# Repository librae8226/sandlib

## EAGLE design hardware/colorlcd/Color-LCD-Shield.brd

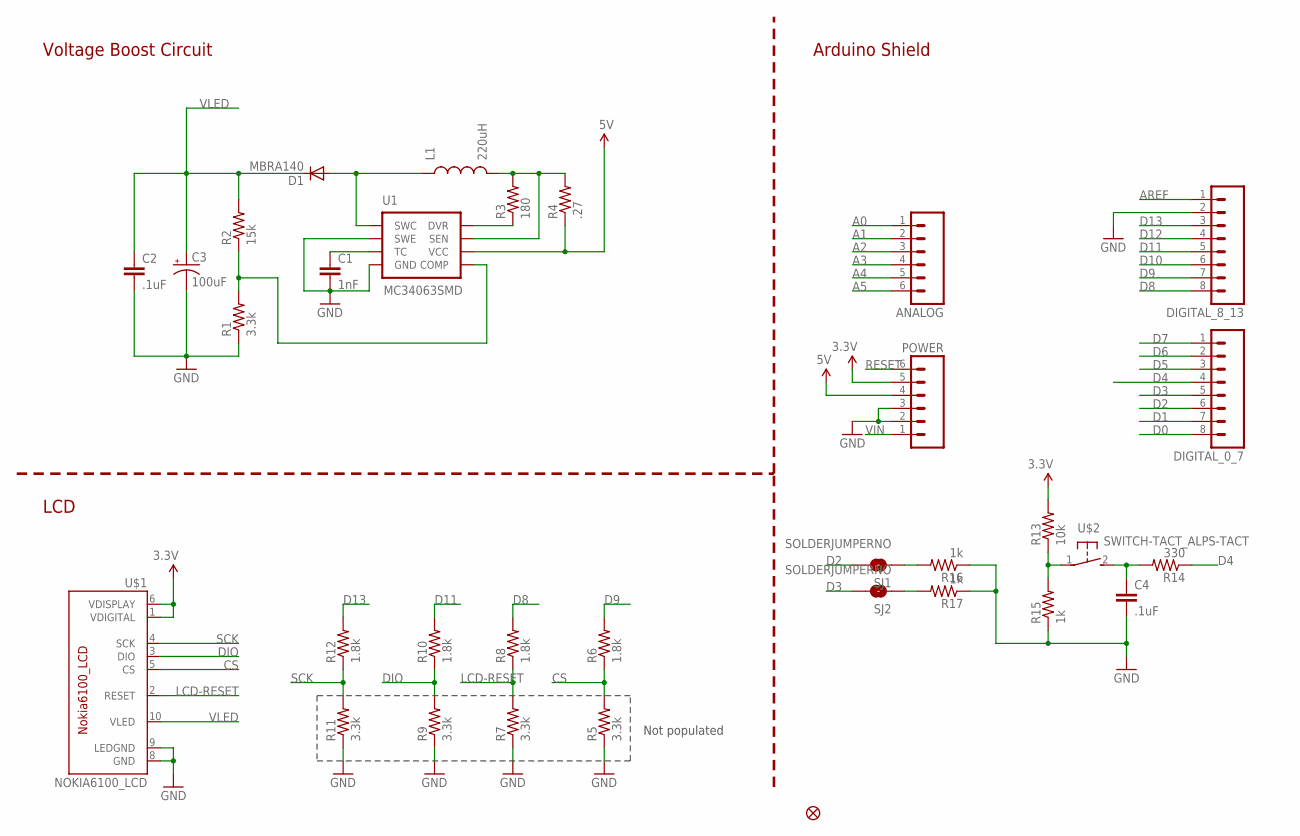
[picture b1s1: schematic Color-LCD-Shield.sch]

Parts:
ANALOG: M06SIP; 1X06
C1: 1nF; 0603-CAP
C2, C4: .1uF; 0603-CAP
C3: 100uF; EIA7343
D1: MBRA140; SMA-DIODE
DIGITAL_0_7, DIGITAL_8_13: M08; 1X08
JP2: FIDUCIAL1X2; FIDUCIAL-1X2
L1: 220uH; NPI75C
POWER: M06SIP; 1X06
R1, R5, R7, R9, R11: 3.3k; 0603-RES
R2: 15k; 0603-RES
R3: 180; 0603-RES
R4: .27; 0603-RES
R6, R8, R10, R12: 1.8k; 0603-RES
R13: 10k; 0603-RES
R14: 330; 0603-RES
R15, R16, R17: 1k; 0603-RES
SJ1, SJ2: SOLDERJUMPERNO; SJ_2S-NO
U1: MC34063SMD; SO08
U$1: NOKIA6100_LCD
U$2: SWITCH-TACT_ALPS-TACT; SWITCH-TACT_DTS-6

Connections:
3.3V: POWER.5, R13.2, U$1.1 (VDIGITAL), U$1.6 (VDISPLAY)
5V: POWER.4, R4.1, U1.6 (VCC)
A0: ANALOG.1
A1: ANALOG.2
A2: ANALOG.3
A3: ANALOG.4
A4: ANALOG.5
A5: ANALOG.6
AREF: DIGITAL_8_13.1
CS: R5.2, R6.1, U$1.5 (CS)
D0: DIGITAL_0_7.8
D1: DIGITAL_0_7.7
D2: DIGITAL_0_7.6, SJ1.2
D3: DIGITAL_0_7.5, SJ2.2
D4: DIGITAL_0_7.4, R14.1
D5: DIGITAL_0_7.3
D6: DIGITAL_0_7.2
D7: DIGITAL_0_7.1
D8: DIGITAL_8_13.8, R8.2
D9: DIGITAL_8_13.7, R6.2
D10: DIGITAL_8_13.6
D11: DIGITAL_8_13.5, R10.2
D12: DIGITAL_8_13.4
D13: DIGITAL_8_13.3, R12.2
DIO: R9.2, R10.1, U$1.3 (DIO)
GND: C1.2, C2.2, C3.C (-), C4.2, DIGITAL_8_13.2, POWER.2, POWER.3, R1.1, R5.1, R7.1, R9.1, R11.1, R15.1, R16.1, R17.1, U1.2 (SWE), U1.4 (GND), U$1.8 (GND), U$1.9 (LEDGND)
LCD-RESET: R7.2, R8.1, U$1.2 (RESET)
unnamed: R13.1, R15.2, U$2.1
unnamed: C4.1, R14.2, U$2.2
unnamed: R17.2, SJ2.1
unnamed: R16.2, SJ1.1
unnamed: R1.2, R2.1, U1.5 (COMP)
unnamed: C1.1, U1.3 (TC)
unnamed: D1.A, L1.1, U1.1 (SWC)
unnamed: R3.1, U1.8 (DVR)
unnamed: L1.2, R3.2, R4.2, U1.7 (SEN)
RESET: POWER.6
SCK: R11.2, R12.1, U$1.4 (SCK)
VIN: POWER.1
VLED: C2.1, C3.A (+), D1.C, R2.2, U$1.10 (VLED)

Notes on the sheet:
Not populated
Voltage Boost Circuit
LCD
Arduino Shield

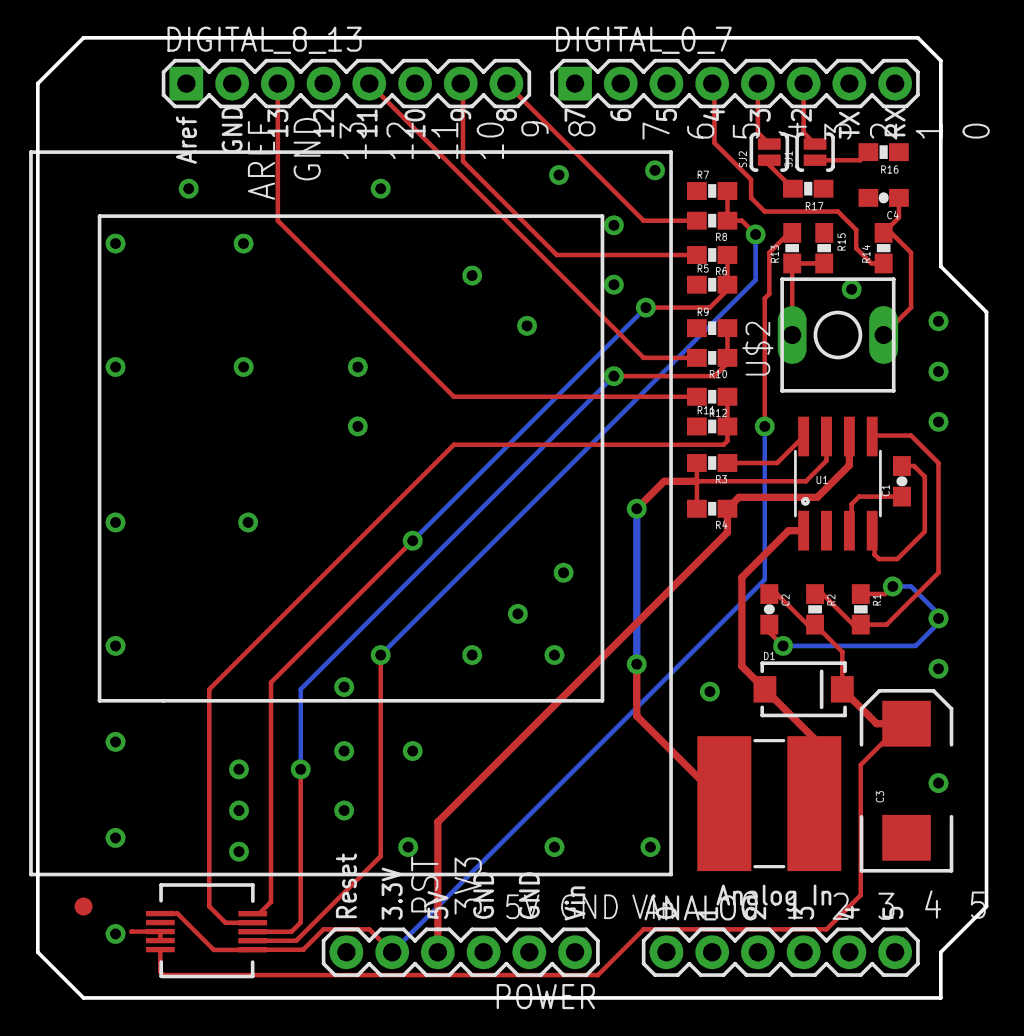
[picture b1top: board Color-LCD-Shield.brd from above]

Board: 2 copper layers, 52.7 x 53.3 mm, 33 parts (0 on the bottom side), 24 nets.

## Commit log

2011-11-17 [update] several legacy test code
    new: affinity_dev, curl_test, sem, shm, thread, url
2011-11-24 add container_of_sample, shell
2011-11-29 add linux_timer sample code
2011-12-02 update affinity_dev
2012-02-24 update curl test code
2012-05-04 update, add kernel gdbg module
2012-05-16 add syscall
2012-06-19 update typo
2012-06-19 add socket (tcp) sample code
2012-06-20 add unix socket sample code
2012-08-31 add kernel doubly linked list sample code
2013-03-06 update shell stuffs
2013-04-27 shell: add dump_eeprom.sh
2013-05-28 add freeglut app and shared lib sample
2013-06-03 Add a readme file for glut-app
2013-07-03 update thread example
2013-07-03 update socket sample code
2013-07-03 update unix socket sample code
2013-07-03 update socket
2013-07-09 add signal sample
2013-07-18 add shell script
2013-07-22 add makefile template for multiple binaries
2013-07-26 longjmp
2013-07-26 update print
2013-08-15 makefile: refine
2013-08-16 update cpu_stat
2013-08-26 add hardware part: color lcd
2014-05-06 add puzzle.c
2014-05-06 add reverse.c and derived penc2ltk.c
2014-05-07 kill warnings in puzzle.c
2014-05-14 add flask tutorial code
2014-05-16 correct penc2ltk
2014-06-07 node sample code
2014-07-28 update flash sample
2014-07-28 update useful scripts
2014-08-27 flask to be accessed externally
2014-09-21 add python
2014-09-22 python: remove red blocks
2014-10-23 sync
2014-10-23 add swapper
2014-10-23 markdown rendered
2014-10-23 add docs
2014-11-02 small cipher code snippets
2014-12-01 python pip click example
2014-12-02 complete basic features of port
2014-12-02 a bit of update for port.py
2014-12-02 port: default to m for eval
2014-12-02 port: refine
2014-12-03 port: add lines for runing directly as a script
2014-12-08 add octave code
2014-12-09 python parse json
2014-12-10 update parse_json, various output format
2014-12-11 get num of items at runtime
2014-12-11 plot total according to date
2014-12-11 add gnuplot html5 canvas demo
2014-12-11 update octave and python
2014-12-12 add plotly
2014-12-12 update plotly_port
2014-12-12 integrate plotly with local json file uploading
2014-12-12 add name for scatter traces in plotly
2014-12-15 pycurl
2014-12-15 adbop push/pull
2014-12-15 pycurl test
2014-12-16 update pycurl test
2014-12-16 remove the hack for plotly
2014-12-17 update python
    pycurl to get last day's changes
    plotly to add growth rate
2014-12-18 add weekly rate
2014-12-19 fix a bug in plotly that we missed weekday() call
2014-12-30 change weekly growth calculation form
    need a more professional algorithm to estimate it
2014-12-31 refine daily growth form
2015-01-05 refine the calculating form for lask week base
2015-01-05 add interpolation
2015-01-05 update data management
    1. update csi300 data
    2. add fetch data script
2015-01-07 typo
2015-01-08 change color of plotly
2015-01-09 add monthly support and refine graph
2015-01-09 revert bar to scatter
2015-01-09 simplify trace name
2015-02-05 update a minor print error
2015-04-09 an ugly landing page for linkgo
2015-05-17 add particle sample commands
2015-05-27 add mqtt stress test script
2015-05-27 clean up python
2015-05-28 debug setsockopt
2015-05-28 avoid bind fail
2015-05-29 while to accept connection and read msg
2015-05-29 update stress
2015-06-01 update server code
2015-07-24 hello.py for mqtt test
2015-07-30 update mqtt stress
2015-11-26 update script
2016-04-15 snapshot index.html for neurite web server
    git hash of neurite repo:
    b58f7d2c781fb806ab784af944d7c54fe399c395
2016-04-15 pthread test
2016-08-15 find_unused_ports_in_range.py
2016-08-19 running learning environment in docker
2016-08-19 finish javascripting
2016-08-21 update Dockerfile and corresponding image
2016-08-22 approaching finishing - node
2016-08-22 use async library to solve this in different ways
2016-08-22 finish learnyounode, touch stream-adventure
2016-08-22 add server.js
2016-08-22 slightly refine json server
2016-08-22 fresh new express app
2016-08-22 modify mapping port to 8080
2016-08-22 express skeleton
2016-08-23 update docker command for learn env
2016-08-23 integrate material ui with running example
    f893414ed2f48864f909a9d537b9f332c65488d8
    examples/browserify-gulp-example (heads/master)
2016-08-23 add example of brunch with react
2016-08-23 fake redirect to '/red'
2016-08-23 refine button and url redirect
2016-08-23 refine container styles
2016-08-29 slightly refine
2016-09-07 add when.promise sample code
2016-10-13 promised exec
2017-01-17 nodejs reverse proxy server
2017-08-12 add mock machine, support async tcp clients
2017-08-13 machine module
2017-08-13 node-nginx-reloader
2017-08-14 mock machine support heartbeat input from args
2017-08-14 update mock machine
2017-08-14 mock machine can reply to cmd
2017-08-15 mock machine handle error
2017-08-17 basic auth node.js client
2018-06-21 add node lab
2021-06-09 go docker for clean addicts

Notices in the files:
parts and their libraries:
SparkFun-Passives: Licensing: CC v3.0 Share-Alike You are welcome to use this library for commercial purposes.
